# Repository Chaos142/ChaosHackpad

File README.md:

# Chaos's Hackpad

### Features
- 128x32 OLED display
- EC11 rotary encoder
- 4 SK6812 RGB LEDs (backlighting)
- 7 MX-Style keys
- WASD and volume controls (firmware will be updated in the future)

### CAD Model:
Screws together using 4 M3 screws.   
Comes in two pieces - the base and the top.  

**Top View**
| Case Open | Case Closed |
|:---------:|:-----------:|
|  |  |

**Side View**
| Case Open | Case Closed |
|:---------:|:-----------:|
|  |  |

### PCB

### Schematic

## Firmware

Runs **CircuitPython** with **KMK firmware** on the **Seeed Studio XIAO RP2040**
The included [firmware](firmware/main.py) file is a temporary firmware used for testing the hardware, and will be changed when I build the board.  
It provides basic key input, rotary encoder volume control, RGB lighting, and OLED display output.  

To install **CircuitPython**, follow [this guide from Seeed Studio](https://wiki.seeedstudio.com/XIAO-RP2040-with-CircuitPython/).  
To install **KMK**, follow [this guide](https://github.com/KMKfw/kmk_firmware/blob/main/docs/en/Getting_Started.md).  

## BOM
- [bom.csv](bom.csv)
- [Interactive PCB BOM](https://htmlpreview.github.io/?https://github.com/Chaos142/ChaosHackpad/blob/main/ibom.html)
- 7x MX-Compatible Uniform Profile Keycaps
- 4x M3x16 Screws
- 1x 3D Printed Case

## [Resources Folder](Resources)
- CustomSwitches.pretty: Cherry MX Switch Footprint with 3D Model
- KiCad-SSD1306-0.91-OLED-4pin-128x32.pretty: [128x32 SSD1306 Footprint](https://github.com/gorbachev/KiCad-SSD1306-0.91-OLED-4pin-128x32.pretty)
- [Seeed Studio XIAO Series Library](https://github.com/Seeed-Studio/OPL_Kicad_Library/tree/master/Seeed%20Studio%20XIAO%20Series%20Library)
- [Fonts Folder](Resources/Fonts): Fonts used for the PCB Silkscreen
- [Models Folder](Resources/Models): 3D models for the KiCad footprints
- SK6812MINI-E: Symbol and footprint libraries for the NeoPixels

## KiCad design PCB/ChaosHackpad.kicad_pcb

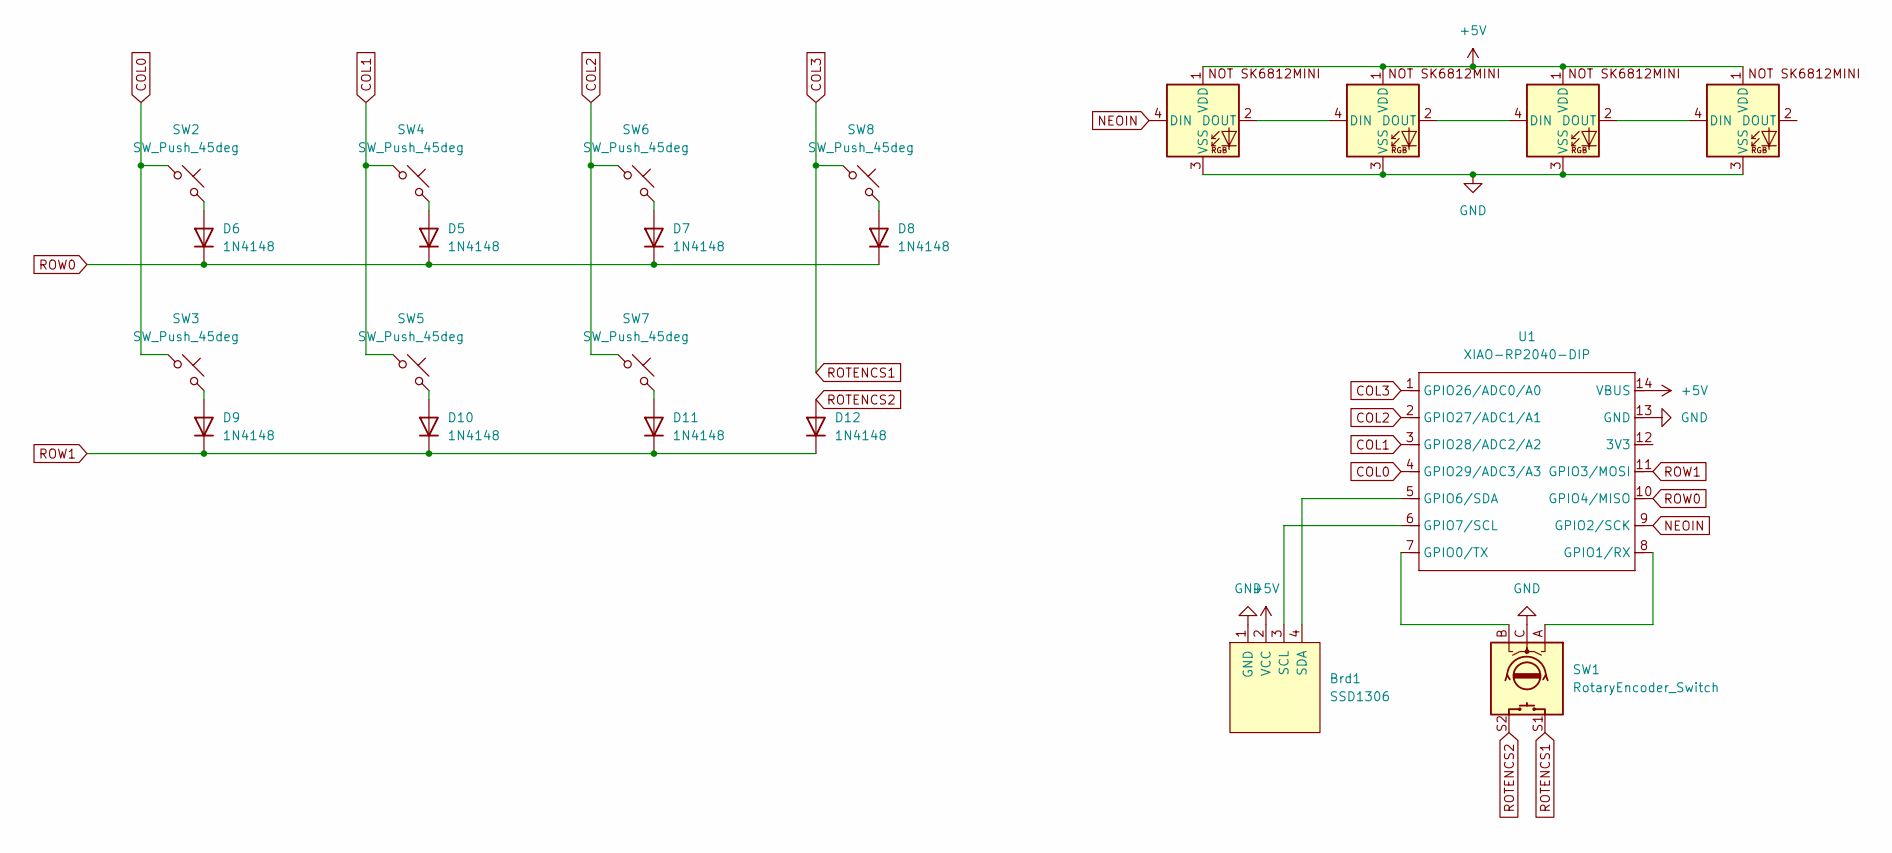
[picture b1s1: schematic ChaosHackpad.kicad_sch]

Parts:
Brd1: SSD1306; SSD1306-0.91-OLED-4pin-128x32
D1, D2, D3, D4: SK6812MINI; SK6812MINI-E_fixed
D5, D6, D7, D8, D9, D10, D11, D12: 1N4148; D_DO-35_SOD27_P7.62mm_Horizontal
SW1: RotaryEncoder_Switch; RotaryEncoder_Alps_EC11E-Switch_Vertical_H20mm
SW2, SW3, SW4, SW5, SW6, SW7, SW8: SW_Push_45deg; SW_Cherry_MX_1.00u_PCB
U1: XIAO-RP2040-DIP

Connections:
+5V: Brd1.2 (VCC), D1.1 (VDD), D2.1 (VDD), D3.1 (VDD), D4.1 (VDD), U1.14 (VBUS)
COL0: SW2.1, SW3.1, U1.4 (GPIO29/ADC3/A3)
COL1: SW4.1, SW5.1, U1.3 (GPIO28/ADC2/A2)
COL2: SW6.1, SW7.1, U1.2 (GPIO27/ADC1/A1)
COL3: SW1.S1, SW8.1, U1.1 (GPIO26/ADC0/A0)
GND: Brd1.1 (GND), D1.3 (VSS), D2.3 (VSS), D3.3 (VSS), D4.3 (VSS), SW1.C, U1.13 (GND)
NEOIN: D1.4 (DIN), U1.9 (GPIO2/SCK)
unnamed: Brd1.3 (SCL), U1.6 (GPIO7/SCL)
unnamed: Brd1.4 (SDA), U1.5 (GPIO6/SDA)
unnamed: D1.2 (DOUT), D2.4 (DIN)
unnamed: D2.2 (DOUT), D3.4 (DIN)
unnamed: D3.2 (DOUT), D4.4 (DIN)
unnamed: D5.2 (A), SW4.2
unnamed: D6.2 (A), SW2.2
unnamed: D7.2 (A), SW6.2
unnamed: D8.2 (A), SW8.2
unnamed: D9.2 (A), SW3.2
unnamed: D10.2 (A), SW5.2
unnamed: D11.2 (A), SW7.2
unnamed: SW1.B, U1.7 (GPIO0/TX)
unnamed: SW1.A, U1.8 (GPIO1/RX)
ROTENCS2: D12.2 (A), SW1.S2
ROW0: D5.1 (K), D6.1 (K), D7.1 (K), D8.1 (K), U1.10 (GPIO4/MISO)
ROW1: D9.1 (K), D10.1 (K), D11.1 (K), D12.1 (K), U1.11 (GPIO3/MOSI)

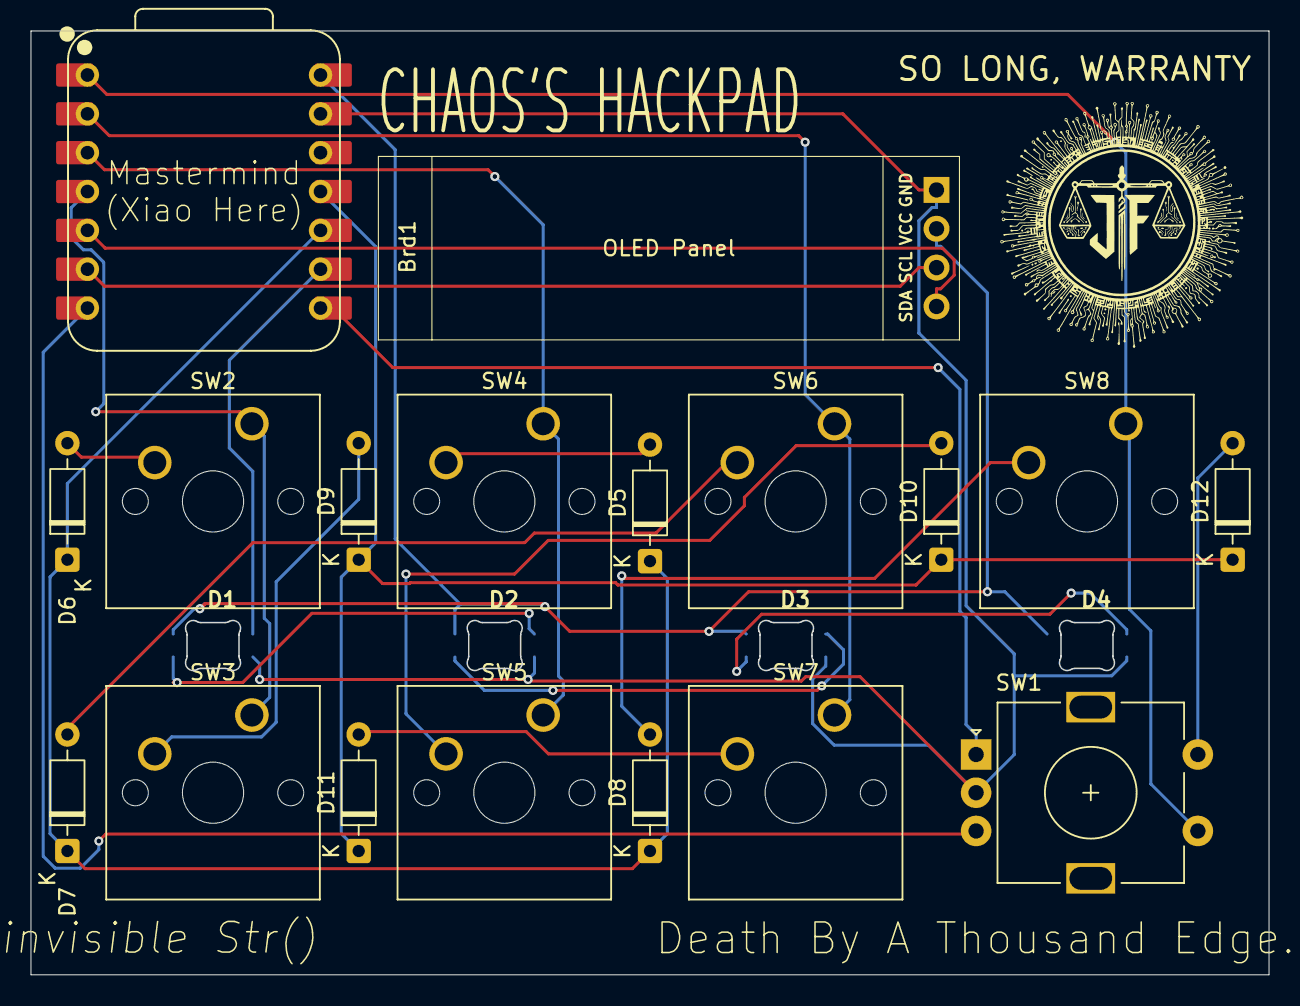
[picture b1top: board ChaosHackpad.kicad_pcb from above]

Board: 2 copper layers, 80.9 x 61.7 mm, 23 parts (0 on the bottom side), 24 nets.

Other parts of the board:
G1: LOGO

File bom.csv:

"Reference","Qty","Value","DNP","Footprint","Datasheet"
"Brd1","1","SSD1306","","KiCad-SSD1306-0.91-OLED-4pin-128x32:SSD1306-0.91-OLED-4pin-128x32","https://www.buydisplay.com/download/manual/ER-OLEDM0.91-1_Da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"
"D1,D2,D3,D4","4","SK6812MINI","","SK6812MINI-E:SK6812MINI-E_fixed","https://cdn-shop.adafruit.com/product-files/4960/4960_SK6812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"
"D5,D6,D7,D8,D9,D10,D11,D12","8","1N4148","","Diode_THT:D_DO-35_SOD27_P7.62mm_Horizontal","https://assets.nexperia.com/documents/data-sheet/1N4148_1N4448.pdf"
"SW1","1","RotaryEncoder_Switch","","Rotary_Encoder:RotaryEncoder_Alps_EC11E-Switch_Vertical_H20mm","https://mm.digikey.com/Volume0/opasdata/d220001/medias/docus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"
"SW2,SW3,SW4,SW5,SW6,SW7,SW8","7","SW_Push_45deg","","CustomSwitches:SW_Cherry_MX_1.00u_PCB","~"
"U1","1","XIAO-RP2040-DIP","","Seeed Studio XIAO Series Library:XIAO-RP2040-DIP","https://files.seeedstudio.com/wiki/XIAO-RP2040/res/rp2040_da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"

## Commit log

2026-01-17 added pcb
2026-01-17 pcb and cad
2026-01-17 firmware
2026-01-20 fixed geeked stuff
2026-01-28 finished
2026-01-28 fixed gitignore
2026-02-03 cleaned up pcb design
2026-02-03 added resources folder
2026-02-03 cleaned up cad
2026-02-03 cleaned up footprints
2026-02-03 renamed and made bom
2026-02-03 better readme
2026-02-03 added 3d models
2026-02-03 updated BOM
2026-02-03 gitignore
2026-02-04 made switches thing global
2026-02-16 rerouted and redesigned PCB, fixed broken footprints/symbols
2026-02-23 added fonts for silkscreen
2026-02-23 fixed fonts
2026-03-13 finished cad and markdown, final submission hopefully
2026-03-13 added firmware info
2026-03-13 fixed readme
2026-03-15 added cad source file
2026-03-28 changed layout
2026-03-31 added gerbers
